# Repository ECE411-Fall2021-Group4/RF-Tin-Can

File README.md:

# RF-Tin-Can
LoFi Walkie Talkie aka LoFi Com Can aka jibber jabber Campbell's Can

Mise en place(everything in its place)

File Organization as it pertains to Nick(our sage git master)
1) If a program creates multiple files, only push the ones ones that are needed for others to use the program (i.e. don't push things like log files)
2) If a program has multiple files, create a folder dedicated to them in the correct spot, ask if you're not sure what the spot is (i.e. if projectlibre has a project file and an image/pdf, create a folder in documentation called "Gantt Chart"
3) Do not keep previous revisions, git does that for us. You can tag the commit of the previous version if you feel inspired (i.e. don't have something like schematic_v1, schematic_v2, shematic_v3. It should just have shematic)
4) If you're not sure what to do, ASK

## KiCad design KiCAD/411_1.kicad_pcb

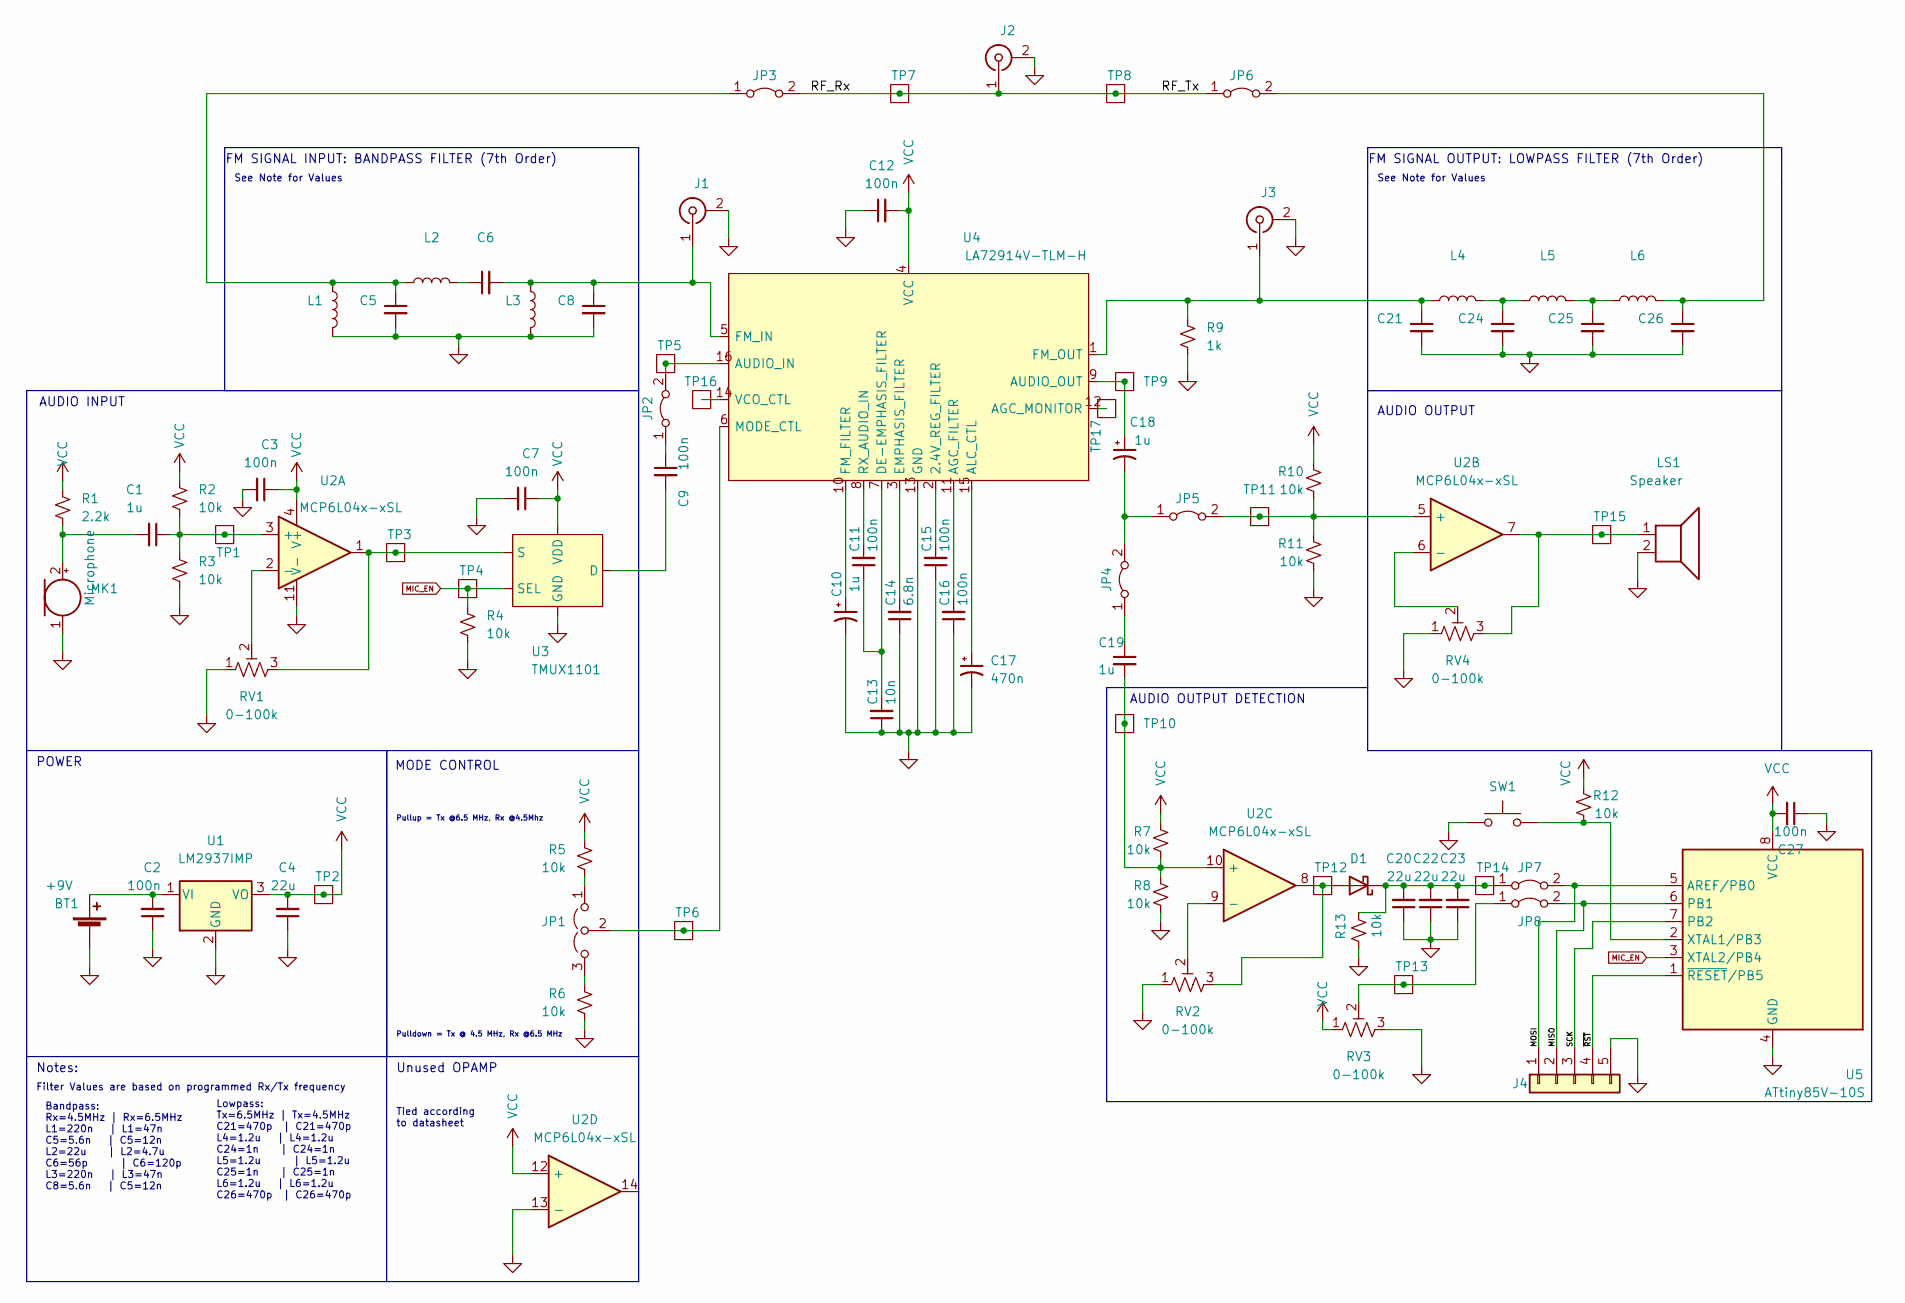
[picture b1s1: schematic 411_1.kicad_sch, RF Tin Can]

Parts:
BT1: +9V; JST_SH_BM02B-SRSS-TB_1x02-1MP_P1.00mm_Vertical
C1, C19: 1u; C_0603_1608Metric_Pad1.08x0.95mm_HandSolder; MPN CL10A105KO8NNNC
C2: 100n; C_0805_2012Metric_Pad1.18x1.45mm_HandSolder; MPN C1608JB0J226M080AC
C3, C7, C9, C11, C12, C15, C16, C27: 100n; C_0603_1608Metric_Pad1.08x0.95mm_HandSolder; MPN C0603C104K4NACAUTO
C4, C20, C22, C23: 22u; C_0805_2012Metric_Pad1.18x1.45mm_HandSolder; MPN C1608JB0J226M080AC
C5, C6, C8: 5.6n; C_0603_1608Metric_Pad1.08x0.95mm_HandSolder; MPN 06035C562KAT2A
C10, C18: 1u; C_Radial_D5.0mm_H5.0mm_P2.00mm; MPN 860020672005
C13: 10n; C_0603_1608Metric_Pad1.08x0.95mm_HandSolder; MPN 0603B103K500CT
C14: 6.8n; C_0603_1608Metric_Pad1.08x0.95mm_HandSolder; MPN CL10B682JB8NNNC
C17: 470n; C_Radial_D5.0mm_H5.0mm_P2.00mm; MPN 860010672004
C21, C24, C25, C26: 470p; C_0603_1608Metric_Pad1.08x0.95mm_HandSolder; MPN CL10B471KB8NNNC
D1: D_Schottky; D_SOD-123; MPN MBR0580S1-7
J1, J3: Conn_Coaxial; U.FL_Molex_MCRF_73412-0110_Vertical; MPN 0734120110
J2: Conn_Coaxial; SMA_Amphenol_132134_Vertical; MPN 132134
J4: Conn_01x05; PinSocket_1x05_P2.54mm_Vertical
JP1: Jumper_3_Open; SolderJumper-3_P1.3mm_Open_Pad1.0x1.5mm; MPN 2011-1X03G00SC028B
JP2, JP3, JP4, JP5, JP6: Jumper; SolderJumper-2_P1.3mm_Open_RoundedPad1.0x1.5mm
JP7: Connector_PinHeader_1.00mm:PinHeader_1x02_P1.00mm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; PinSocket_1x02_P2.54mm_Vertical
JP8: Jumper_2_Bridged; PinSocket_1x02_P2.54mm_Vertical
L1, L2, L3: 220n; C_0603_1608Metric_Pad1.08x0.95mm_HandSolder; MPN 0603DC-R22XJRW
L4, L5, L6: 3.3u; C_0603_1608Metric_Pad1.08x0.95mm_HandSolder; MPN CWF1610-3R3K
LS1: Speaker; PinSocket_1x02_P2.54mm_Vertical; MPN 1890
MK1: Microphone; PinSocket_1x02_P2.54mm_Vertical; MPN CMEJ-4618-42-L015
R1: 2.2k; R_0603_1608Metric_Pad0.98x0.95mm_HandSolder; MPN RT0603FRE132K2L
R2, R3, R4, R5, R6, R7, R8, R10, R11, R12, R13: 10k; R_0603_1608Metric_Pad0.98x0.95mm_HandSolder; MPN RT0603FRE132K2L
R9: 1k; R_0603_1608Metric_Pad0.98x0.95mm_HandSolder; MPN RT0603FRE132K2L
RV1, RV2, RV3, RV4: 0-100k; Potentiometer_Bourns_3314R-1_Vertical_Hole; MPN 3361P-1-104GLF
SW1: SW_Push; PinSocket_1x02_P2.54mm_Vertical
TP1, TP2, TP3, TP4, TP5, TP6, TP7, TP8, TP9, TP10, TP11, TP12, TP13, TP14, TP15, TP16, TP17: Testpoint; PinHeader_1x01_P1.00mm_Vertical
U1: LM2937IMP; SOT-223-3_TabPin2; MPN LM2937IMP-5.0
U2: MCP6L04x-xSL; SOIC-14_3.9x8.7mm_P1.27mm
U3: TMUX1101; SOT-23-5_HandSoldering; MPN 74HC4053PW,118
U4: LA72914V-TLM-H; TSSOP-16_4.4x5mm_P0.65mm; MPN LA72914V-TLM-H
U5: ATtiny85V-10S; SOIC-8W_5.3x5.3mm_P1.27mm; MPN ATTINY85-20SUR

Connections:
/MISO: J4.2, JP8.2 (B), U5.6 (PB1)
/MOSI: J4.1, JP7.2 (B), U5.5 (AREF/PB0)
/RF_Rx: J2.1 (In), JP3.2 (B), JP6.1 (A), TP7.1, TP8.1
/SCK: J4.3, U5.7 (PB2)
/~RST: J4.4, U5.1 (~RESET/PB5)
GND: BT1.2 (-), C2.1, C3.2, C4.1, C5.2, C7.2, C8.2, C10.2, C12.1, C13.1, C14.1, C15.1, C16.1, C17.2, C20.1, C21.2, C22.1, C23.1, C24.2, C25.2, C26.2, C27.1, J1.2 (Ext), J2.2 (Ext), J3.2 (Ext), J4.5, L1.1, L3.1, LS1.2, MK1.1 (-), R3.1, R4.1, R6.2, R8.2, R9.1, R11.2, R13.2, RV1.1, RV2.1, RV3.3, RV4.1, SW1.1, U1.2 (GND), U2.11 (V-), U2.13 (-), U3.3 (GND), U4.13 (GND), U5.4 (GND)
MIC_EN: R4.2, TP4.1, U3.4 (SEL), U5.3 (XTAL2/PB4)
unnamed: BT1.1 (+), C2.2, U1.1 (VI)
unnamed: C1.1, R2.1, R3.2, TP1.1, U2.3 (+)
unnamed: C1.2, MK1.2 (+), R1.1
unnamed: C5.1, JP3.1 (A), L1.2, L2.2
unnamed: C6.1, L2.1
unnamed: C6.2, C8.1, J1.1 (In), L3.2, U4.5 (FM_IN)
unnamed: C9.1, JP2.1 (A)
unnamed: C9.2, U3.1 (D)
unnamed: C11.1, C13.2, U4.7 (DE-EMPHASIS_FILTER)
unnamed: C11.2, U4.8 (RX_AUDIO_IN)
unnamed: C14.2, U4.3 (EMPHASIS_FILTER)
unnamed: C15.2, U4.2 (2.4V_REG_FILTER)
unnamed: C16.2, U4.11 (AGC_FILTER)
unnamed: C17.1, U4.15 (ALC_CTL)
unnamed: C19.1, JP4.1 (A)
unnamed: C19.2, R7.2, R8.1, TP10.1, U2.10 (+)
unnamed: C20.2, C22.2, C23.2, D1.1 (K), JP7.1 (A), R13.1, TP14.1
unnamed: C21.1, J3.1 (In), L4.2, R9.2, U4.1 (FM_OUT)
unnamed: C24.1, L4.1, L5.2
unnamed: C25.1, L5.1, L6.2
unnamed: C26.1, JP6.2 (B), L6.1
unnamed: D1.2 (A), RV2.3, TP12.1, U2.8
unnamed: JP1.1 (A), R5.2
unnamed: JP1.2 (C), TP6.1, U4.6 (MODE_CTL)
unnamed: JP1.3 (B), R6.1
unnamed: JP2.2 (B), TP5.1, U4.16 (AUDIO_IN)
unnamed: C18.2, JP4.2 (B), JP5.1 (A)
unnamed: JP5.2 (B), R10.2, R11.1, TP11.1, U2.5 (+)
unnamed: JP8.1 (A), RV3.2, TP13.1
unnamed: LS1.1, RV4.3, TP15.1, U2.7
unnamed: R12.2, SW1.2, U5.2 (XTAL1/PB3)
unnamed: RV1.2, U2.2 (-)
unnamed: RV1.3, TP3.1, U2.1, U3.2 (S)
unnamed: RV2.2, U2.9 (-)
unnamed: RV4.2, U2.6 (-)
unnamed: C18.1, TP9.1, U4.9 (AUDIO_OUT)
unnamed: TP16.1, U4.14 (VCO_CTL)
unnamed: TP17.1, U4.12 (AGC_MONITOR)
unnamed: C10.1, U4.10 (FM_FILTER)
VCC: C3.1, C4.2, C7.1, C12.2, C27.2, R1.2, R2.2, R5.1, R7.1, R10.1, R12.1, RV3.1, TP2.1, U1.3 (VO), U2.4 (V+), U2.12 (+), U3.5 (VDD), U4.4 (VCC), U5.8 (VCC)

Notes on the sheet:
POWER
Notes:
Filter Values are based on programmed Rx/Tx frequency
Bandpass: Rx=4.5MHz | Rx=6.5MHz L1=220n | L1=47n C5=5.6n | C5=12n L2=22u | L2=4.7u C6=56p | C6=120p L3=220n | L3=47n C8=5.6n | C5=12n
AUDIO INPUT
Lowpass: Tx=6.5MHz | Tx=4.5MHz C21=470p | C21=470p L4=1.2u | L4=1.2u C24=1n | C24=1n L5=1.2u | L5=1.2u C25=1n | C25=1n L6=1.2u | L6=1.2u C26=470p | C26=470p
See Note for Values
Pullup = Tx @6.5 MHz, Rx @4.5Mhz
Pulldown = Tx @ 4.5 MHz, Rx @6.5 MHz
Unused OPAMP
Tied according to datasheet
MODE CONTROL
FM SIGNAL INPUT: BANDPASS FILTER (7th Order)
AUDIO OUTPUT DETECTION
FM SIGNAL OUTPUT: LOWPASS FILTER (7th Order)
AUDIO OUTPUT

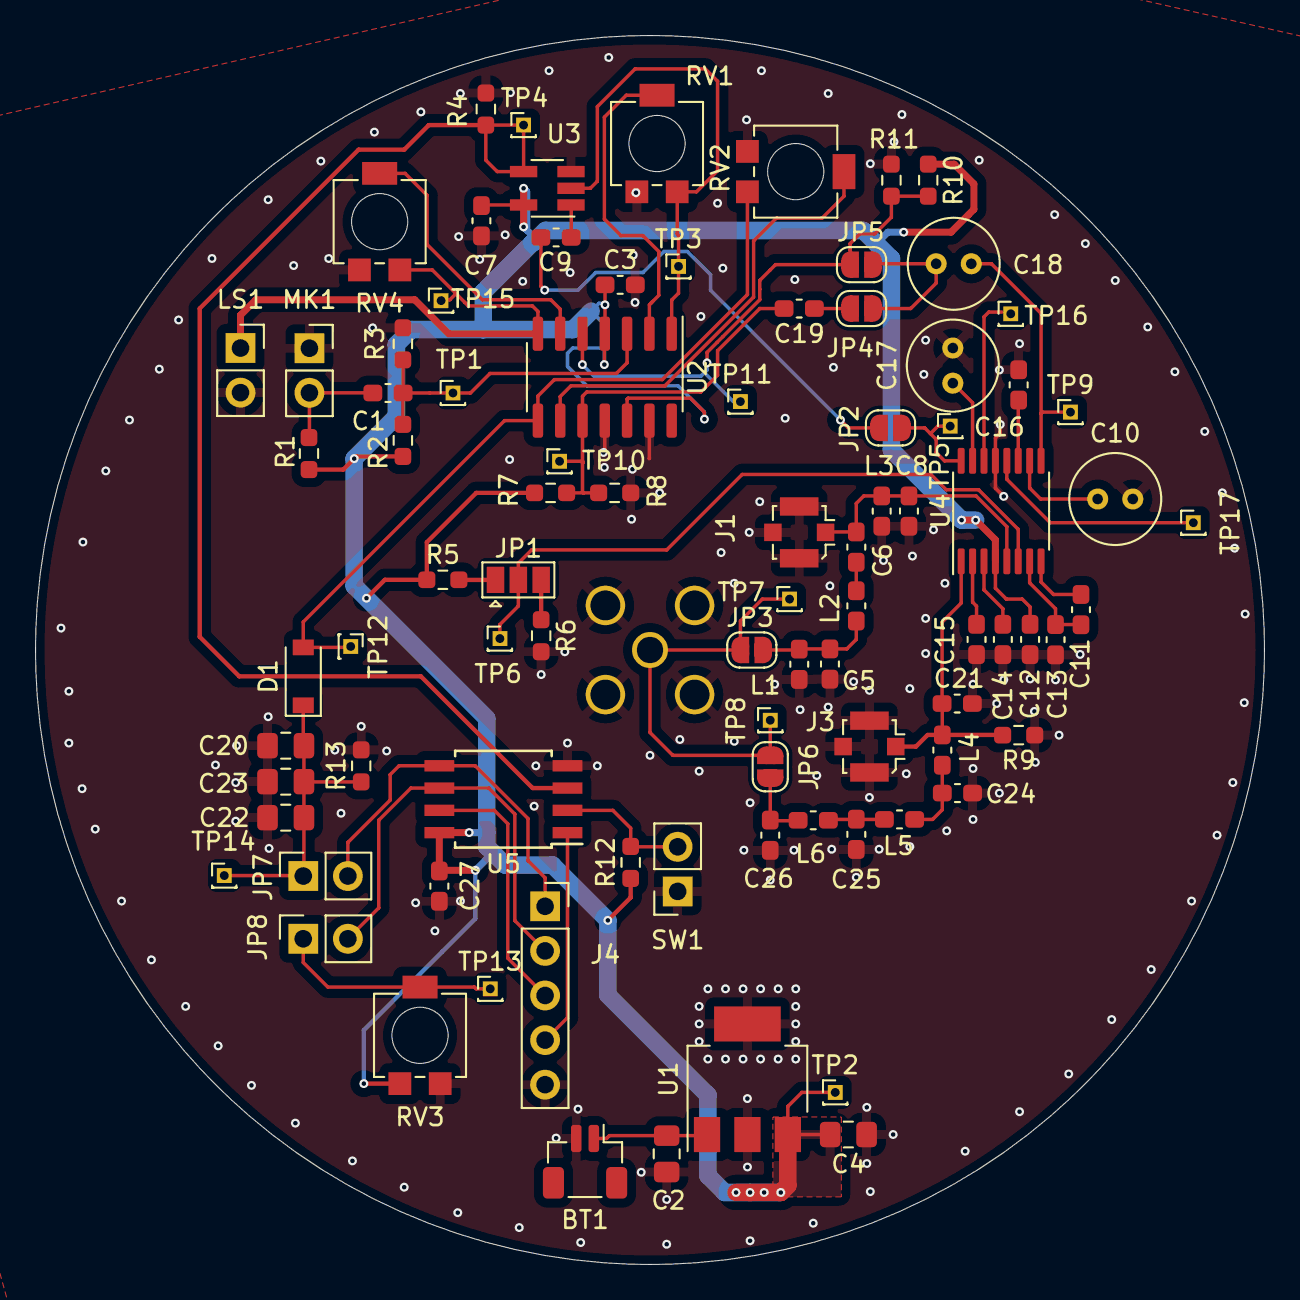
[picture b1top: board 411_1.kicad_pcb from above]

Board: 2 copper layers, 70.0 x 70.0 mm, 89 parts (1 on the bottom side), 47 nets.

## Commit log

2021-11-03 organized repo
2021-11-03 Syd Test a thing
2021-11-03 Deleted the dum thing
2021-11-03 Added Chip .lib file
2021-11-03 Added BPF
2021-11-04 Create GANTT Chart
2021-11-04 Updated schematic with all of the things. Started preliminary layout
2021-11-04 Schedule
    Gantt charts from ProjectLibre.
2021-11-04 Create Schedule
2021-11-04 Create ECE 411 Team 4 Gantt Chart
2021-11-07 added BOM for week 7
2021-11-07 deleted BOM :(
2021-11-09 Added LPF and BPF from Spice
2021-11-10 Add files via upload
    Added two IO Signal filters, Mode Control jumper for 6.5MHz=Vcc, 4.5MHz=GND
2021-11-18 Rev 1.0 shipped to oshpark
2021-11-23 Added info to components for bom generation
2021-11-24 Fixed look up values for filter values
2021-11-24 generated BOMS for both boards
2021-12-02 Add files via upload
    By the hands of God aka David.
2021-12-03 Added 3D print STL
    Added 3D print STL
2021-12-06 Create ATtiny85 Code
2021-12-06 Rename documentation/ECE_411_Practicum_Project_ATtiny85_Micro_controller.ino to ATtiny85_Code.ino
2021-12-07 Printed schematic pdf
